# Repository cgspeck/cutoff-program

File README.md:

# 3D Printer Power control system

This allows a Raspberry Pi running [OctoPrint](https://octoprint.org/) and the [PSU Control Plugin](https://plugins.octoprint.org/plugins/psucontrol/) to control the power supply to a 3D printer.

There is a connection for a [12V network smoke detector](https://www.aliexpress.com/item/32850855553.html?spm=a2g0s.9042311.0.0.27424c4dtptgRe). The smoke detector must be connected, and in a good state, for the power to turn on.

---

**WARNING AND DISCLAIMER**

There is no guarantee whatsoever that this unit will function as intended and there is no responsibility on my part.

Further, working with mains electricity has its own inherent risks. If you attempt this project then you assume all responsibility

---

## How it functions

Once built the Arduino brains of the circuit is connected to some GPIO pins of a Raspberry Pi running Octoprint via the level shifter component.

When power is first connected a startup phase runs for four seconds, during which the alert buzzer & signal will be tested.

After startup, a two-way centre-off toggle switch determines whether the printer:

- is powered on by manual demand (up)
- is off (center)
- is powered on demand by a connected Raspberry Pi (down)

A second toggle switch determines whether the extraction fan:

- is powered on demand by a connected Raspberry Pi (up)
- is off (center)
- is slaved to the printer's power status (down)

The extraction fan will be powered unless the printer is powered.

If the smoke detector is triggered, or gets disconnected:

- power to the printer is cut off
- power to the extraction fan is cut off
- the buzzer is sounded constantly
- an alert signal is sent to the Raspberry Pi

The only way to recover the system once triggered is via the reset button.

You should supply power to the power control system, Pi, printer, extraction fan and all via Saftey Switch/RCBO/GFCI breaker in order to protect yourself and also render the system incapable of automatically starting up in the event of loss, and resumption, of mains electrical supply/

## Development

### Development Prerequisites

- [Arduino IDE >= 1.8.4](https://www.arduino.cc/en/Main/Software)

- [Arduino-Makefile](https://github.com/sudar/Arduino-Makefile)

- [direnv](https://direnv.net/) for managing arduino & avr library and tool locations if the defaults don't work

The version of Arduino in the Ubuntu repository is ancient and will not work. Consider using `scripts/install-deps.sh` which uses [umake](https://github.com/ubuntu/ubuntu-make) to install up to date Arduino environment.

### Handy Hints

Building, uploading and starting the monitor: `make`

To quit the monitor (gnu screen): `CTRL + A`, `:quit`.

VS Code Intelligence not working? Check [this post](https://github.com/Microsoft/vscode-arduino/issues/438#issuecomment-345362087).

### Typical paths

The default paths in `./Makefile` are for Ubuntu.

Typical paths for OSX, with Arduino-Makefile installed via Homebrew, are (`.envrc`):

```bash
export ARDUINO_DIR=/Applications/Arduino.app/Contents/Java
export ARDMK_DIR=/usr/local/opt/arduino-mk
export AVR_TOOLS_DIR=/Applications/Arduino.app/Contents/Java/hardware/tools/avr
export AVRDUDE=/Applications/Arduino.app/Contents/Java/hardware/tools/avr/bin/avrdude
export AVRDUDE_CONF=/Applications/Arduino.app/Contents/Java/hardware/tools/avr/etc/avrdude.conf
```

### As-built Pins

| RPI (GPIO/BCM) | Interface Circuit                                                |
| -------------- | ---------------------------------------------------------------- |
| 26 (brown)     | Fan Power (inverted, low = on, only works if printer is powered) |
| 23 (green)     | Printer Power (inverted, low = on)                               |
| 24 (yellow)    | alarm state?                                                     |
| GND (orange)   | GND                                                              |
| 25 (red)       | Printer State (high = on)                                        |

## License

Arduino 3d printer cut off program
Copyright (C) 2019 Christopher Speck

This program is free software: you can redistribute it and/or modify
it under the terms of the GNU General Public License as published by
the Free Software Foundation, either version 3 of the License, or
(at your option) any later version.

This program is distributed in the hope that it will be useful,
but WITHOUT ANY WARRANTY; without even the implied warranty of
MERCHANTABILITY or FITNESS FOR A PARTICULAR PURPOSE. See the
GNU General Public License for more details.

You should have received a copy of the GNU General Public License
along with this program. If not, see <https://www.gnu.org/licenses/>.

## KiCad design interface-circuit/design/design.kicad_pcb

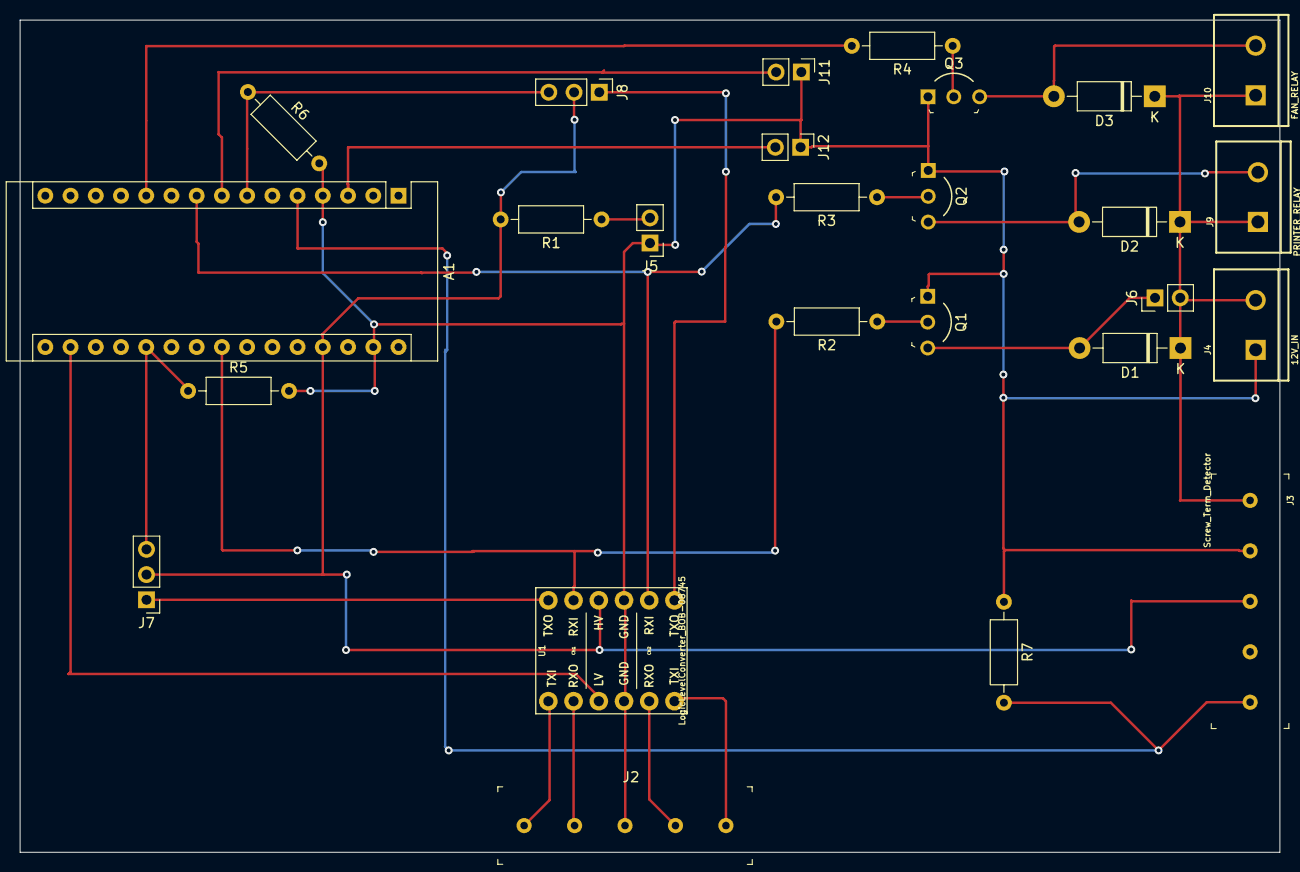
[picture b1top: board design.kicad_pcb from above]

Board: 2 copper layers, 126.8 x 83.8 mm, 26 parts (0 on the bottom side), 25 nets.

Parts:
A1: Arduino_Nano_v3.x; Arduino_Nano
D1, D2, D3: 1N4007; D_DO-41_SOD81_P10.16mm_Horizontal
J2: Screw_Term_RPi; Term_Block_1x5_P5.08mm
J3: Screw_Term_Detector; Term_Block_1x5_P5.08mm
J4: 12V_IN; SCREWTERMINAL-5MM-2
J5: Conn_Pwr_LED; PinHeader_1x02_P2.54mm_Vertical
J6: Conn_Piezo; PinHeader_1x02_P2.54mm_Vertical
J7: Conn_Printer_Mode; PinHeader_1x03_P2.54mm_Vertical
J8: Conn_Fan_Mode; PinHeader_1x03_P2.54mm_Vertical
J9: PRINTER_RELAY; SCREWTERMINAL-5MM-2
J10: FAN_RELAY; SCREWTERMINAL-5MM-2
J11: Conn_Switch; PinHeader_1x02_P2.54mm_Vertical
J12: Conn_Reset; PinHeader_1x02_P2.54mm_Vertical
Q1, Q2, Q3: 2N3904-AP; TO-92-3_Formed_Leads
R1: 220R; R_Axial_DIN0207_L6.3mm_D2.5mm_P10.16mm_Horizontal
R2, R3, R4: 560R; R_Axial_DIN0207_L6.3mm_D2.5mm_P10.16mm_Horizontal
R5, R6, R7: 10R; R_Axial_DIN0207_L6.3mm_D2.5mm_P10.16mm_Horizontal
U1: LogicLevelConverter_BOB-08745; LOGIC_LEVEL_CONVERTER_BOB-8745

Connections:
+3V3: A1.17, U1.6
+5V: A1.27, J3.3, J7.2, J8.2, R1.2, U1.5
+12V: D1.1, D2.1, D3.1, J3.1, J4.2, J6.2, J9.1, J10.1
/-PIEZO: D1.2, J6.1, Q1.3
/D7_PRINTER_RELAY: A1.9, R3.2, U1.2
/D8_FAN_RELAY: A1.11, R4.2
/DETECTOR_SIGNAL: A1.5, J3.5, R7.2
/HV_AlarmTriggered: A1.23, R2.2, U1.1
/HV_FanPowerDemand: J8.1, U1.12
/HV_PrinterPowerDemand: J7.1, U1.11
/LV_AlarmTriggered: J2.2, U1.9
/LV_FanPowerDemand: J2.5, U1.4
/LV_PrinterPowerDemand: J2.1, U1.3
/LV_PrinterPowerStatus: J2.4, U1.10
/RESET: A1.3, J12.2
/SOFT_SWITCH: A1.8, J11.2
/SW_FAN_RELAY: A1.7, J8.3, R6.1
/SW_PRINTER_RELAY: A1.20, J7.3, R5.1
GND: A1.4, A1.29, J2.3, J3.2, J4.1, J5.1, J11.1, J12.1, Q1.1, Q2.1, Q3.1, R5.2, R6.2, R7.1, U1.7, U1.8
unnamed: D2.2, J9.2, Q2.3
unnamed: D3.2, J10.2, Q3.3
unnamed: J5.2, R1.1
unnamed: Q1.2, R2.1
unnamed: Q2.2, R3.1
unnamed: Q3.2, R4.1

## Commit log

2018-09-21 Initial commit with firmware for Arduino
2019-04-07 prototype code for breadboard
2019-04-10 Make sure previousPiFanPwrDemand is updated
2019-04-10 Further minimise the amount of pins used
2019-04-12 Trying out Arduino-Makefile project
2019-04-13 Configured VS Code search paths
2019-04-13 Some additional make targets, remove platform io
2019-04-13 This builds, uploads and starts the monitor
2019-04-13 Added readme
2019-04-18 Allow it to build on OSX and get rid of platformio reminants
2019-04-18 Switch to a Nano
2019-04-18 Remove redundant variables
2019-04-24 Rely on the detector's nc signal to indicate everything is ok
2019-04-24 Adding a push button that must be pressed to start the system
2019-04-24 Actually have it work on the nano I have
2019-04-24 Ensure serial report is run
2019-04-25 Fleshing out circuit specifications
2019-04-25 Use internal pullup resistor on soft button instead of external pull down
2019-04-25 wip - transistor switches done
2019-04-25 Terminals for three-way switches, and 12v adaptor
2019-04-26 Finished design and ERC passes
2019-04-26 Removed connectors between Arduino and shifter, header strips will be soldered in under them
2019-04-26 Cleanup
2019-04-26 Associated all components that will go on the protoboard
2019-04-26 Had to number pins on custom footprint to get netlist to work
2019-04-26 Cannot get the custom component to work, flipped in pcb new and labels associated with wrong sides
2019-04-27 Done with manual routing
2019-04-27 Aligned nano on board
2019-04-27 Fix 'no submodule mapping found'
2019-05-03 I realised that the detector was being bypassed by the switches so the switches have been moved to the input side of the arduino.
2019-05-03 Fixed issue where net was incorrectly attached to arduino
2019-05-05 Move printer power demand and relay output to analoge pins to distribute the traces across the board
2019-05-05 Swap Alert & Printer relay pins on arduino to simplify routing
2019-05-05 Changed protoboard layout so that we are using pins from both sides of the Arduino
2019-05-05 Printouts of PCB
2019-05-31 Removed unattended start wip because this is already better done in hardware with a RCD
2019-05-31 Panel templates
2019-05-31 update templates
2019-05-31 Finish up templates
2019-06-02 Template for bottom of power supply
2019-06-03 Remove debouncing lib temp
2019-06-03 Refer pin 15 not A0
2019-06-03 Fix issue with fan not turning on and off
2019-06-03 Fix fan logic
2019-06-04 This is also A1
2019-06-04 Actually set up the pin
2019-06-04 No need to convert to a const here
2019-06-07 OSX Make Configuration
2019-06-07 Reverse logic and set up internal pullups
2019-06-23 Updating eschema with pull down resistors on Arduino inputs
2019-06-23 adding cable colours to diagram
2019-06-23 Updated protoboard layout to match rough implementation
2019-06-23 Clean up
2019-06-23 Adding license
2019-06-23 Kicad design (#3)
2019-10-02 This didn't appear to do anything
2019-10-02 This didn't appear to do anything (#4)
2019-10-02 Insert a 1.5 second delay between smoke alarm going off and power being cut
2019-10-02 Insert a 1.5 second delay between smoke alarm going off and power being cut (#5)
2019-10-02 Reduce startup time to 3 seconds
2019-10-13 Increase trigger delay to 2 seconds
2019-10-13 Allow alarm to be turned off remotely by cycling power domand pin
2021-04-18 Recording as-built pins on the Pi
2021-04-18 Add an SVG of circuit so I can refer to it without needing Kicad
